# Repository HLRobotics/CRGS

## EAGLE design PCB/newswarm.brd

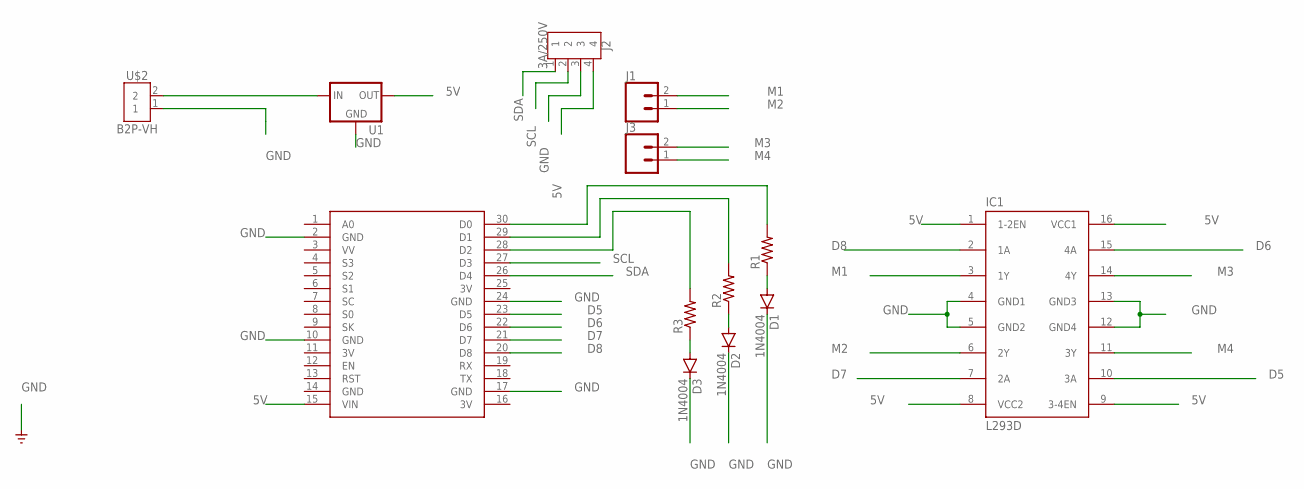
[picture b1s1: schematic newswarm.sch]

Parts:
D1, D2, D3: 1N4004; DO41-10
IC1: L293D; DIL16
J1, J3: CONN_02; 1X02
J2: 3A/250V; B4B-XH-A
R1, R2, R3: R-US_0207/10; 0207/10
U1: V_REG_78XXSIDE; 78XXL
U$1: NODEMCU
U$2: B2P-VH; B2P-VH_396-2N

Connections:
3V: U$1.11 (3V), U$1.16 (3V), U$1.25 (3V)
5V: IC1.1 (1-2EN), IC1.8 (VCC2), IC1.9 (3-4EN), IC1.16 (VCC1), J2.4, U1.OUT, U$1.15 (VIN)
D5: IC1.10 (3A), U$1.23 (D5)
D6: IC1.15 (4A), U$1.22 (D6)
D7: IC1.7 (2A), U$1.21 (D7)
D8: IC1.2 (1A), U$1.20 (D8)
GND: D1.C, D2.C, D3.C, IC1.4 (GND1), IC1.5 (GND2), IC1.12 (GND4), IC1.13 (GND3), J2.3, U1.GND, U$1.2 (GND), U$1.10 (GND), U$1.14 (GND), U$1.17 (GND), U$1.24 (GND), U$2.1
M1: IC1.3 (1Y), J1.2
M2: IC1.6 (2Y), J1.1
M3: IC1.14 (4Y), J3.2
M4: IC1.11 (3Y), J3.1
unnamed: R1.2, U$1.30 (D0)
unnamed: D1.A, R1.1
unnamed: U1.IN, U$2.2
unnamed: R2.2, U$1.29 (D1)
unnamed: R3.2, U$1.28 (D2)
unnamed: D3.A, R3.1
unnamed: D2.A, R2.1
SCL: J2.2, U$1.27 (D3)
SDA: J2.1, U$1.26 (D4)

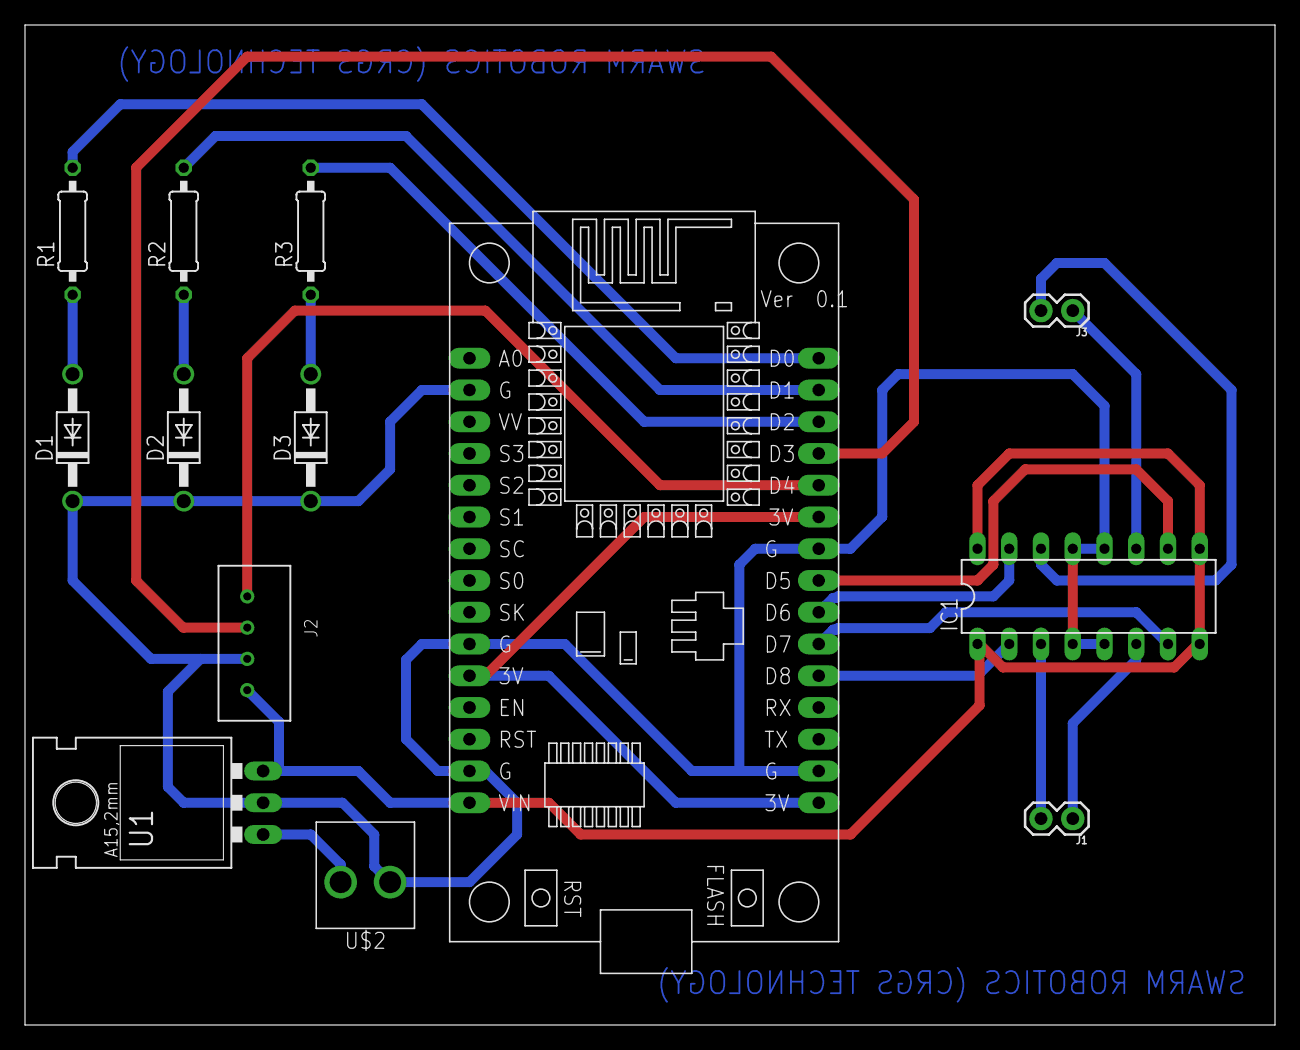
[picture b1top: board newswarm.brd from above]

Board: 2 copper layers, 100.0 x 80.0 mm, 13 parts (0 on the bottom side), 20 nets.

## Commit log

2022-05-11 Mian Branch commit

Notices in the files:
parts and their libraries:
SparkFun-IC-Power: Licensing: Creative Commons ShareAlike 4.0 International - https://creativecommons.org/licenses/by-sa/4.0
